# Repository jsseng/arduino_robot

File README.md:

arduino_robot
=============

A controllable arduino robot aimed towards elementary students to get them introduced
to computing at an early age. Comes with firmware and software including a
custom programming language tailored for simple use by students. The grammar
is defined [here](PurelyGrammar.pdf).

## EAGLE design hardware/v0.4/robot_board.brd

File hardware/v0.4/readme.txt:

Note:  Excellon drill file resolution at 5 digits

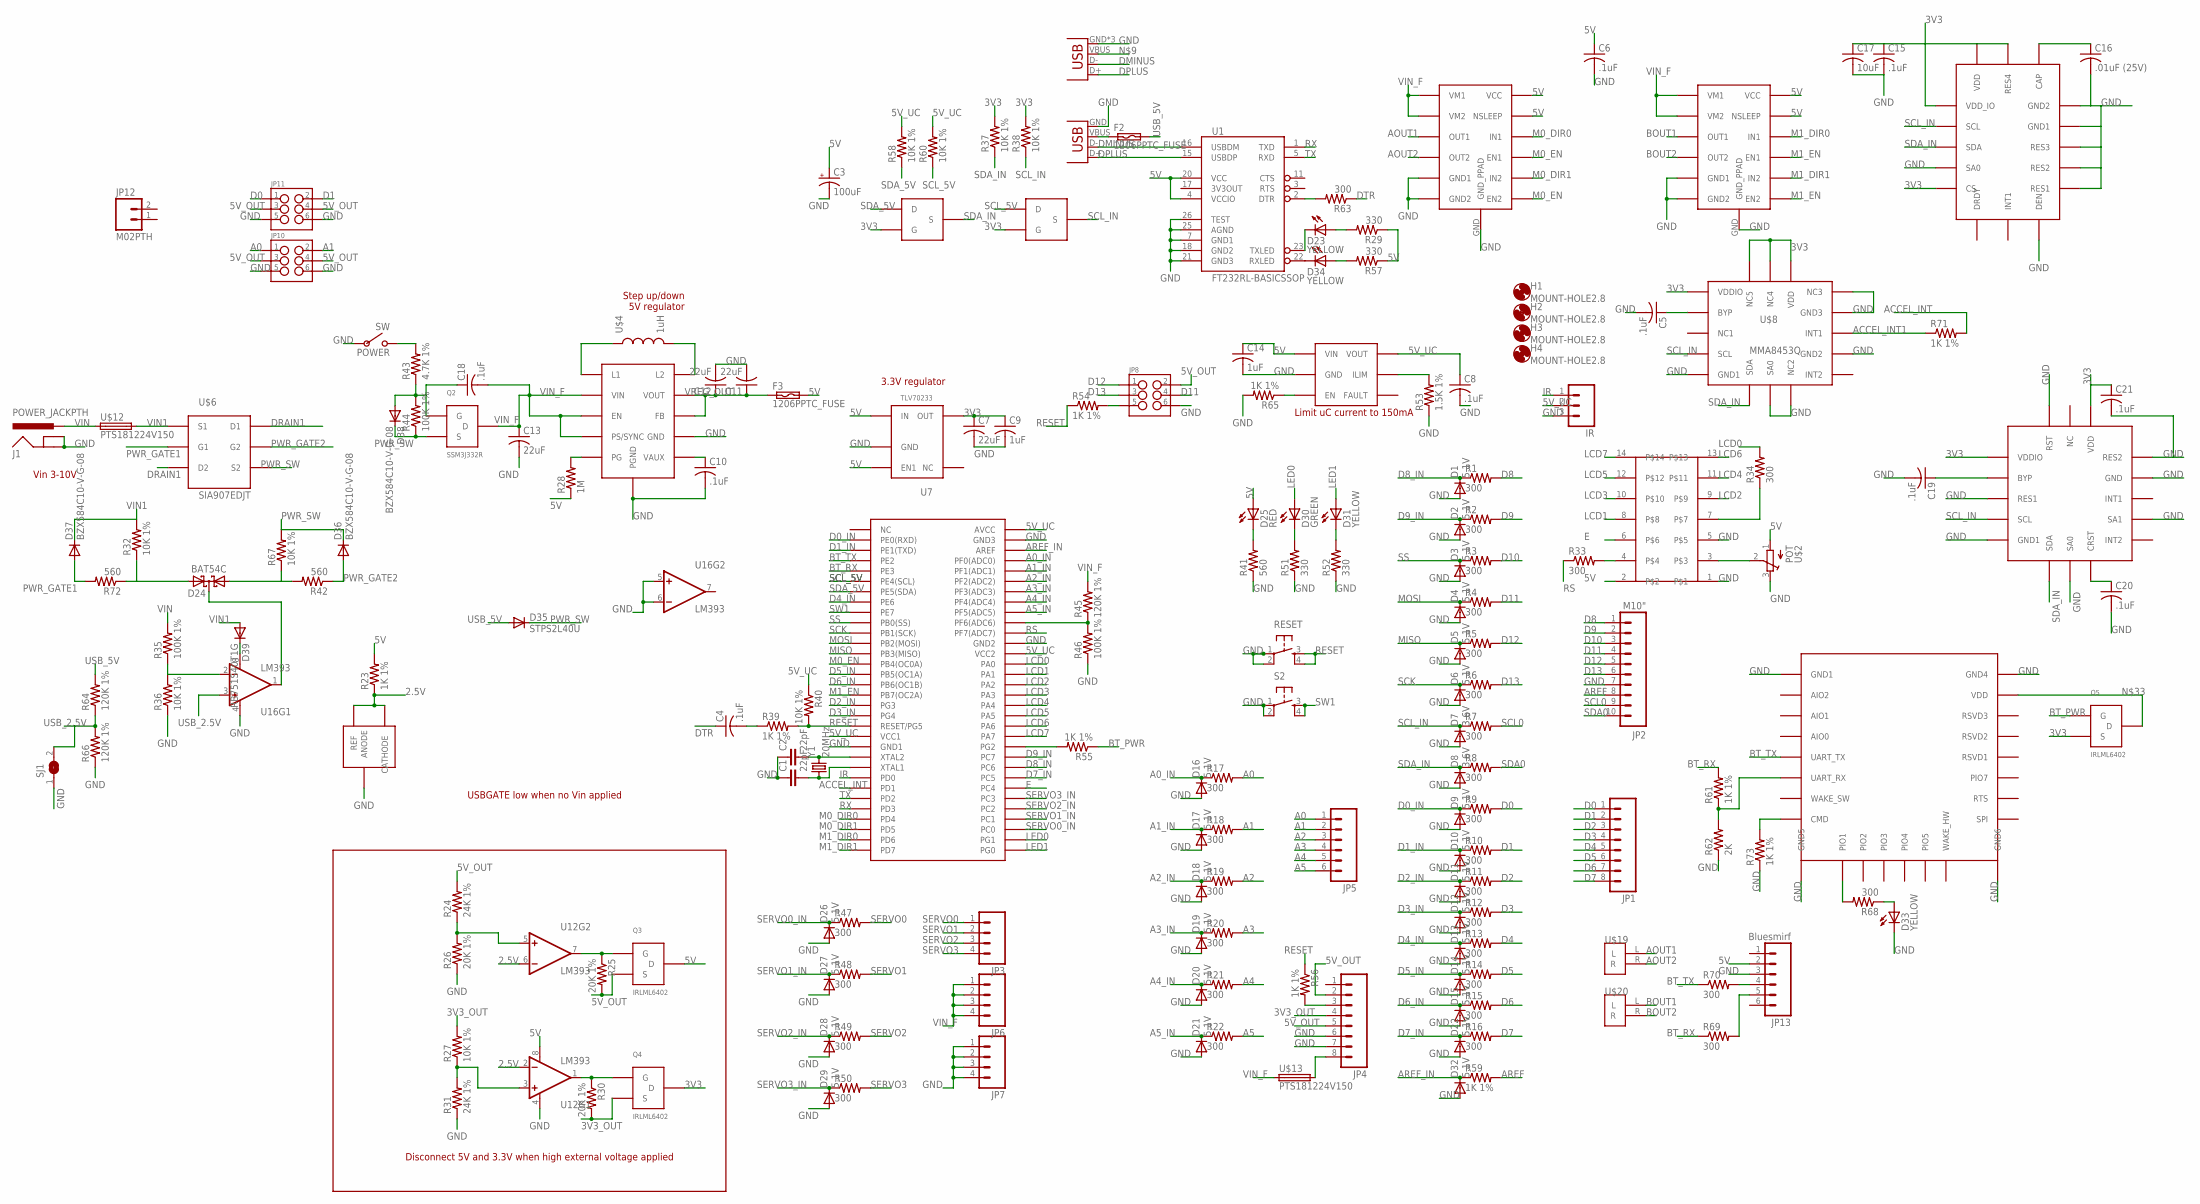
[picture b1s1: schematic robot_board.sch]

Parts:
C1, C2: 22pF; 0805
C3: 100uF; PANASONIC_D
C4, C5, C6, C8, C10, C15, C18, C19, C20, C21: .1uF; C1206
C7, C11, C12, C13: 22uF; C1206
C9, C14: 1uF; C1206
C16: .01uF (25V); C1206
C17: 10uF; C1206
D1, D2, D3, D4, D5, D6, D9, D10, D11, D12, D13, D14, D15, D16, D17, D18, D19, D20, D21, D22, D26, D27, D28, D29, D32: 5.1V; SOT23-3
D7, D8: 3.6V; SOT23-3
D23, D31, D33, D34: YELLOW; LED-1206
D24: BAT54C; SOT23
D25: RED; LED-1206
D30: GREEN; LED-1206
D35: STPS2L40U; SMA-DIODE
D36, D37, D38: BZX584C10-V-G-08; SOD523
D39: RB751S40T1G; SOD523
F2, F3: 1206PPTC_FUSE; R1206
H1, H2, H3, H4: MOUNT-HOLE2.8; 2,8
IR: M03PTH; 1X03
J1: POWER_JACKPTH; POWER_JACK_PTH
JP1, JP4: M081X08; 1X08
JP2: M10"; 1X10
JP3, JP6, JP7: M04PTH; 1X04
JP5: M06SIP; 1X06
JP8, JP10, JP11: M03X22X3_SILK_SM; 2X3
JP9: USB-B; USB-B-PTH
JP12: M02PTH; 1X02
JP13: Bluesmirf; 1X06
JP14: USB-MICROB
POWER: SW
Q2: SSM3J332R; SOT23
Q3, Q4, Q5: IRLML6402; SOT23
R1, R2, R3, R4, R5, R6, R7, R8, R9, R10, R11, R12, R13, R14, R15, R16, R17, R18, R19, R20, R21, R22, R33, R34, R47, R48, R49, R50, R63, R68, R69, R70: 300; R1206
R23, R39, R54, R55, R56, R59, R61, R65, R71, R73: 1K 1%; R1206
R24, R31: 24K 1%; R1206
R25, R26, R30: 20K 1%; R1206
R27, R32, R36, R37, R38, R40, R58, R60, R67: 10K 1%; R1206
R28: 1M; R1206
R29, R51, R52, R57: 330; R1206
R35, R44, R46: 100K 1%; R1206
R41, R42, R72: 560; R1206
R43: 4.7K 1%; R1206
R45, R64, R66: 120K 1%; R1206
R53: 1.5K 1%; R1206
R62: 2K; R1206
RESET: TAC_SWITCHPTH; TACTILE-PTH
S2: TAC_SWITCHPTH; TACTILE-PTH
SJ1: SJW
U1: FT232RL-BASICSSOP; SSOP28DB
U7: TLV70233; SOT-23-5
U8: MIC2009A; SOT23-M5
U9, U10: DRV8839; PWSON-N12
U12, U16: LM393; SO08
U17: ATMEGA325PA; TQFP64
U$1: 2X7HEADER; 2X7
U$2: POT
U$3: TPS63061; WSON-10
U$4: 1uH; TAIYO4012
U$5: AP431SAG-7; SOT23
U$6: SIA907EDJT; SC70T
U$7: RN4020; RN4020_PKG
U$8: MMA8453Q; QFN-COL
U$9, U$10: BSS138; SOT23
U$11: L3GD20HTR; LGA-16
U$12, U$13: PTS181224V150; C1812
U$14: FXOS8700CQ; FSOS8700CQ_PKG
U$19, U$20: 2POS_TERMINAL
Y1: 20MHz; CRYSTAL-SMD-10.5X4.8-2PIN

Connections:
2.5V: R23.1, U12.2 (-IN), U12.6 (-IN), U$5.1 (CATHODE), U$5.2 (REF)
3V3: C7.1, C9.1, C15.1, C17.1, C21.1, Q4.3 (D), Q5.2 (S), R37.2, R38.2, U7.P$4 (OUT), U$8.P$1 (VDDIO), U$8.P$14 (VDD), U$8.P$15 (NC4), U$8.P$16 (NC5), U$9.1 (G), U$10.1 (G), U$11.P$1 (VDD_IO), U$11.P$5 (CS), U$11.P$15 (RES4), U$11.P$16 (VDD), U$14.P$1 (VDDIO), U$14.P$14 (VDD)
3V3_OUT: JP4.4, Q4.2 (S), R27.2, R30.2
5V: C3.+, C6.1, C14.1, D25.A, F3.2, JP13.2, Q3.3 (D), R23.2, R28.1, R29.1, R57.1, U1.4 (VCCIO), U1.20 (VCC), U7.P$1 (IN), U7.P$3 (EN1), U8.P$1 (VIN), U9.P$7 (VCC), U9.P$8 (NSLEEP), U10.P$7 (VCC), U10.P$8 (NSLEEP), U12.8 (V+), U$1.2, U$2.1 (A)
5V_OUT: JP4.2, JP4.5, JP8.2, JP10.3, JP10.4, JP11.3, JP11.4, Q3.2 (S), R24.2, R25.2
5V_UC: C8.1, IR.2, R40.1, R58.2, R60.2, U8.P$6 (VOUT), U17.21 (VCC1), U17.52 (VCC2), U17.64 (AVCC)
A0: JP5.1, JP10.1, R17.2
A0_IN: D16.3 (C), R17.1, U17.61 (PF0(ADC0))
A1: JP5.2, JP10.2, R18.2
A1_IN: D17.3 (C), R18.1, U17.60 (PF1(ADC1))
A2: JP5.3, R19.2
A2_IN: D18.3 (C), R19.1, U17.59 (PF2(ADC2))
A3: JP5.4, R20.2
A3_IN: D19.3 (C), R20.1, U17.58 (PF3(ADC3))
A4: JP5.5, R21.2
A4_IN: D20.3 (C), R21.1, U17.57 (PF4(ADC4))
A5: JP5.6, R22.2
A5_IN: D21.3 (C), R22.1, U17.56 (PF5(ADC5))
ACCEL_INT: R71.2, U17.26 (PD1)
ACCEL_INT1: R71.1, U$8.P$11 (INT1)
AOUT1: U9.P$3 (OUT1), U$19.L
AOUT2: U9.P$4 (OUT2), U$19.R
AREF: JP2.8, R59.2
AREF_IN: D32.3 (C), R59.1, U17.62 (AREF)
BOUT1: U10.P$3 (OUT1), U$20.L
BOUT2: U10.P$4 (OUT2), U$20.R
BT_PWR: Q5.1 (G), R55.1
BT_RX: R61.2, R69.1, U17.5 (PE3)
BT_TX: R70.1, U17.4 (PE2), U$7.P$5 (UART_TX)
D0: JP1.1, JP11.1, R9.2
D0_IN: D9.3 (C), R9.1, U17.2 (PE0(RXD))
D1: JP1.2, JP11.2, R10.2
D1_IN: D10.3 (C), R10.1, U17.3 (PE1(TXD))
D2: JP1.3, R11.2
D2_IN: D11.3 (C), R11.1, U17.18 (PG3)
D3: JP1.4, R12.2
D3_IN: D12.3 (C), R12.1, U17.19 (PG4)
D4: JP1.5, R13.2
D4_IN: D13.3 (C), R13.1, U17.8 (PE6)
D5: JP1.6, R14.2
D5_IN: D14.3 (C), R14.1, U17.15 (PB5(OC1A))
D6: JP1.7, R15.2
D6_IN: D15.3 (C), R15.1, U17.16 (PB6(OC1B))
D7: JP1.8, R16.2
D7_IN: D22.3 (C), R16.1, U17.40 (PC5)
D8: JP2.1, R1.2
D8_IN: D1.3 (C), R1.1, U17.41 (PC6)
D9: JP2.2, R2.2
D9_IN: D2.3 (C), R2.1, U17.42 (PC7)
D10: JP2.3, R3.2
D11: JP2.4, JP8.4, R4.2
D12: JP2.5, JP8.1, R5.2
D13: JP2.6, JP8.3, R6.2
DMINUS: JP9.D-, JP14.D-, U1.16 (USBDM)
DPLUS: JP9.D+, JP14.D+, U1.15 (USBDP)
DRAIN1: U$6.D1@1 (D1), U$6.D1@2 (D1), U$6.D2@1 (D2), U$6.D2@2 (D2)
DTR: C4.1, R63.1
E: U17.39 (PC4), U$1.6
GND: C1.1, C2.1, C3.-, C5.2, C6.2, C7.2, C8.2, C9.2, C10.2, C11.2, C12.2, C13.2, C14.2, C15.2, C16.2, C17.2, C19.2, C20.2, C21.2, D1.1 (A), D2.1 (A), D3.1 (A), D4.1 (A), D5.1 (A), D6.1 (A), D7.1 (A), D8.1 (A), D9.1 (A), D10.1 (A), D11.1 (A), D12.1 (A), D13.1 (A), D14.1 (A), D15.1 (A), D16.1 (A), D17.1 (A), D18.1 (A), D19.1 (A), D20.1 (A), D21.1 (A), D22.1 (A), D26.1 (A), D27.1 (A), D28.1 (A), D29.1 (A), D32.1 (A), D33.C, IR.3, J1.GND, J1.GNDBREAK, JP2.7, JP4.6, JP4.7, JP7.1, JP7.2, JP7.3, JP7.4, JP8.6, JP9.GND, JP10.5, JP10.6, JP11.5, JP11.6, JP13.3, JP14.GND, JP14.MT1 (GND), JP14.MT2 (GND), POWER.P$2, R26.1, R31.1, R36.1, R41.1, R46.1, R51.1, R52.1, R53.1, R62.1, R65.2, R66.1, R73.1, RESET.1, RESET.2, S2.1, S2.2, SJ1.1, U1.7 (GND1), U1.18 (GND2), U1.21 (GND3), U1.25 (AGND), U1.26 (TEST), U7.P$2 (GND), U8.P$2 (GND), U9.GND (GND_PPAD), U9.P$5 (GND1), U9.P$6 (GND2), U10.GND (GND_PPAD), U10.P$5 (GND1), U10.P$6 (GND2), U12.4 (V-), U16.4 (V-), U16.5 (+IN), U16.6 (-IN), U17.22 (GND1), U17.53 (GND2), U17.63 (GND3), U$1.1, U$1.5, U$2.3 (E), U$3.GND@N1 (PGND), U$3.GND@N2 (PGND), U$3.GND@N3 (PGND), U$3.GND@N4 (PGND), U$3.GND@N5 (PGND), U$3.GND@N6 (PGND), U$3.GND@N7 (PGND), U$3.GND@N8 (PGND), U$3.P$7 (GND), U$3.P$11 (PGND), U$5.3 (ANODE), U$7.P$1 (GND1), U$7.P$22 (GND4), U$7.P$23 (GND5), U$7.P$24 (GND6), U$8.P$5 (GND1), U$8.P$7 (SA0), U$8.P$8 (NC2), U$8.P$10 (GND2), U$8.P$12 (GND3), U$8.P$13 (NC3), U$11.P$4 (SA0), U$11.P$8 (DEN), U$11.P$9 (RES1), U$11.P$10 (RES2), U$11.P$11 (RES3), U$11.P$12 (GND1), U$11.P$13 (GND2), U$14.P$3 (RES1), U$14.P$5 (GND1), U$14.P$7 (SA0), U$14.P$10 (SA1), U$14.P$12 (GND), U$14.P$13 (RES2), U$14.P$16 (RST)
IR: IR.1, U17.25 (PD0)
LCD0: R34.2, U17.51 (PA0)
LCD1: U17.50 (PA1), U$1.8
LCD2: U17.49 (PA2), U$1.9
LCD3: U17.48 (PA3), U$1.10
LCD4: U17.47 (PA4), U$1.11
LCD5: U17.46 (PA5), U$1.12
LCD6: U17.45 (PA6), U$1.13
LCD7: U17.44 (PA7), U$1.14
LED0: D30.A, U17.34 (PG1)
LED1: D31.A, U17.33 (PG0)
M0_DIR0: U9.P$9 (IN1), U17.29 (PD4)
M0_DIR1: U9.P$11 (IN2), U17.30 (PD5)
M0_EN: U9.P$10 (EN1), U9.P$12 (EN2), U17.14 (PB4(OC0A))
M1_DIR0: U10.P$9 (IN1), U17.31 (PD6)
M1_DIR1: U10.P$11 (IN2), U17.32 (PD7)
M1_EN: U10.P$10 (EN1), U10.P$12 (EN2), U17.17 (PB7(OC2A))
MISO: D5.3 (C), R5.1, U17.13 (PB3(MISO))
MOSI: D4.3 (C), R4.1, U17.12 (PB2(MOSI))
unnamed: C2.2, U17.23 (XTAL2), Y1.P$2 (2)
unnamed: C1.2, U17.24 (XTAL1), Y1.P$1 (1)
unnamed: R53.2, U8.P$5 (ILIM)
unnamed: R55.2, U17.43 (PG2)
unnamed: JP4.3, R56.2
unnamed: C5.1, U$8.P$2 (BYP)
unnamed: F2.1, JP9.VBUS, JP14.VBUS
unnamed: D34.C, U1.22 (RXLED)
unnamed: D34.A, R57.2
unnamed: D23.A, R29.2
unnamed: R61.1, R62.2, U$7.P$6 (UART_RX)
unnamed: R63.2, U1.2 (DTR)
unnamed: U$1.3, U$2.2 (S)
unnamed: R28.2, U$3.P$5 (PG)
unnamed: R65.1, U8.P$3 (EN)
unnamed: D24.3 (CC), U16.1 (OUT)
unnamed: C10.1, U$3.P$6 (VAUX)
unnamed: U$3.P$1 (L1), U$4.P$1 (1)
unnamed: U$3.P$10 (L2), U$4.P$2 (2)
unnamed: D23.C, U1.23 (TXLED)
unnamed: D24.2 (A2), R32.1, R72.1
unnamed: D24.1 (A1), R42.2, R67.1
unnamed: R33.2, U$1.4
unnamed: R34.1, U$1.7
unnamed: C4.2, R39.1
unnamed: JP4.8, U$13.2
unnamed: JP8.5, R54.2
unnamed: Q3.1 (G), R25.1, U12.7 (OUT)
unnamed: R68.2, U$7.P$9 (PIO1)
unnamed: D33.A, R68.1
unnamed: Q5.3 (D), U$7.P$21 (VDD)
unnamed: R24.1, R26.2, U12.5 (+IN)
unnamed: JP13.4, R70.2
unnamed: JP13.5, R69.2
unnamed: C16.1, U$11.P$14 (CAP)
unnamed: R27.1, R31.2, U12.3 (+IN)
unnamed: R35.1, R36.2, U16.2 (-IN)
unnamed: D25.C, R41.2
unnamed: D39.C, U16.8 (V+)
unnamed: POWER.P$1, R43.2
unnamed: C19.1, U$14.P$2 (BYP)
unnamed: Q4.1 (G), R30.1, U12.1 (OUT)
unnamed: R73.2, U$7.P$8 (CMD)
unnamed: C20.1, U$14.P$8 (CRST)
unnamed: C18.1, D38.A, Q2.1 (G), R43.1, R44.2
unnamed: R45.1, R46.2, U17.55 (PF6(ADC6))
unnamed: D30.C, R51.2
unnamed: D31.C, R52.2
PWR_GATE1: D37.A, R72.2, U$6.G1
PWR_GATE2: D36.A, R42.1, U$6.G2
PWR_SW: D35.C, D36.C, D38.C, Q2.2 (S), R44.1, R67.2, U$6.S2
RESET: R39.2, R40.2, R54.1, R56.1, RESET.3, RESET.4, U17.20 (RESET/PG5)
RS: R33.1, U17.54 (PF7(ADC7))
RX: U1.1 (TXD), U17.28 (PD3)
SCK: D6.3 (C), R6.1, U17.11 (PB1(SCK))
SCL0: JP2.9, R7.2
SCL_5V: R60.1, U17.6 (PE4(SCL)), U$10.3 (D)
SCL_IN: D7.3 (C), R7.1, R38.1, U$8.P$4 (SCL), U$10.2 (S), U$11.P$2 (SCL), U$14.P$4 (SCL)
SDA0: JP2.10, R8.2
SDA_5V: R58.1, U17.7 (PE5(SDA)), U$9.3 (D)
SDA_IN: D8.3 (C), R8.1, R37.1, U$8.P$6 (SDA), U$9.2 (S), U$11.P$3 (SDA), U$14.P$6 (SDA)
SERVO0: JP3.1, R47.2
SERVO0_IN: D26.3 (C), R47.1, U17.35 (PC0)
SERVO1: JP3.2, R48.2
SERVO1_IN: D27.3 (C), R48.1, U17.36 (PC1)
SERVO2: JP3.3, R49.2
SERVO2_IN: D28.3 (C), R49.1, U17.37 (PC2)
SERVO3: JP3.4, R50.2
SERVO3_IN: D29.3 (C), R50.1, U17.38 (PC3)
SS: D3.3 (C), R3.1, U17.10 (PB0(SS))
SW1: S2.3, S2.4, U17.9 (PE7)
TX: U1.5 (RXD), U17.27 (PD2)
USB_2.5V: R64.1, R66.2, SJ1.2, U16.3 (+IN)
USB_5V: D35.A, F2.2, R64.2
VIN: J1.PWR, R35.2, U$12.1
VIN1: D37.C, D39.A, R32.2, U$6.S1, U$12.2
VIN_F: C13.1, C18.2, JP6.1, JP6.2, JP6.3, JP6.4, Q2.3 (D), R45.2, U9.P$1 (VM1), U9.P$2 (VM2), U10.P$1 (VM1), U10.P$2 (VM2), U$3.P$2 (VIN), U$3.P$3 (EN), U$3.P$4 (PS/SYNC), U$13.1
VREG_OUT: C11.1, C12.1, F3.1, U$3.P$8 (FB), U$3.P$9 (VOUT)

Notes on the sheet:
USBGATE low when no Vin applied
3.3V regulator
Disconnect 5V and 3.3V when high external voltage applied
Limit uC current to 150mA
Step up/down 5V regulator
Vin 3-10V

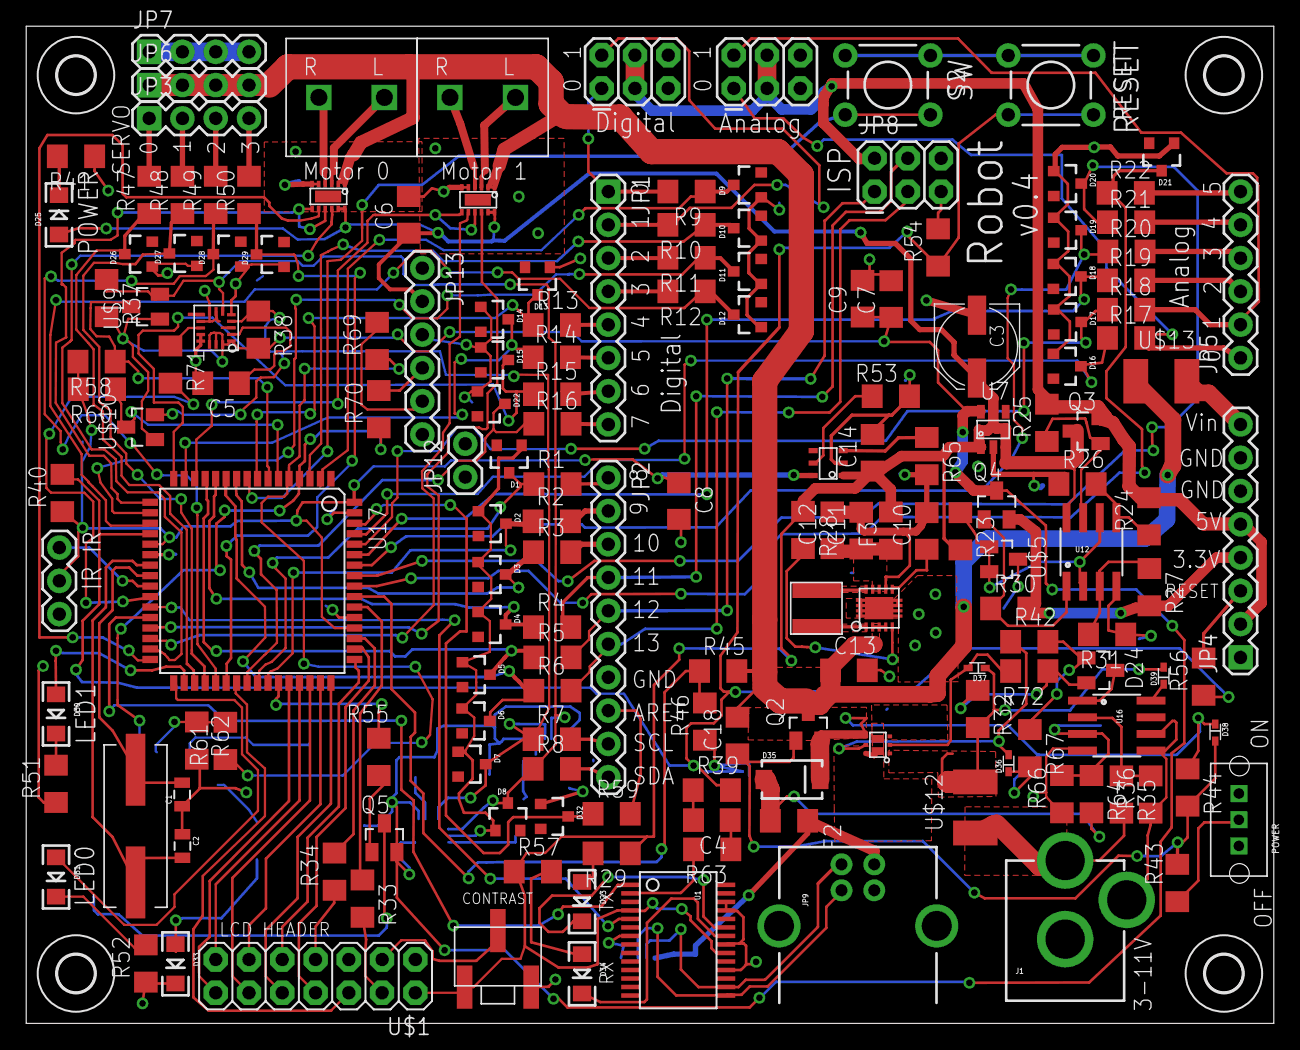
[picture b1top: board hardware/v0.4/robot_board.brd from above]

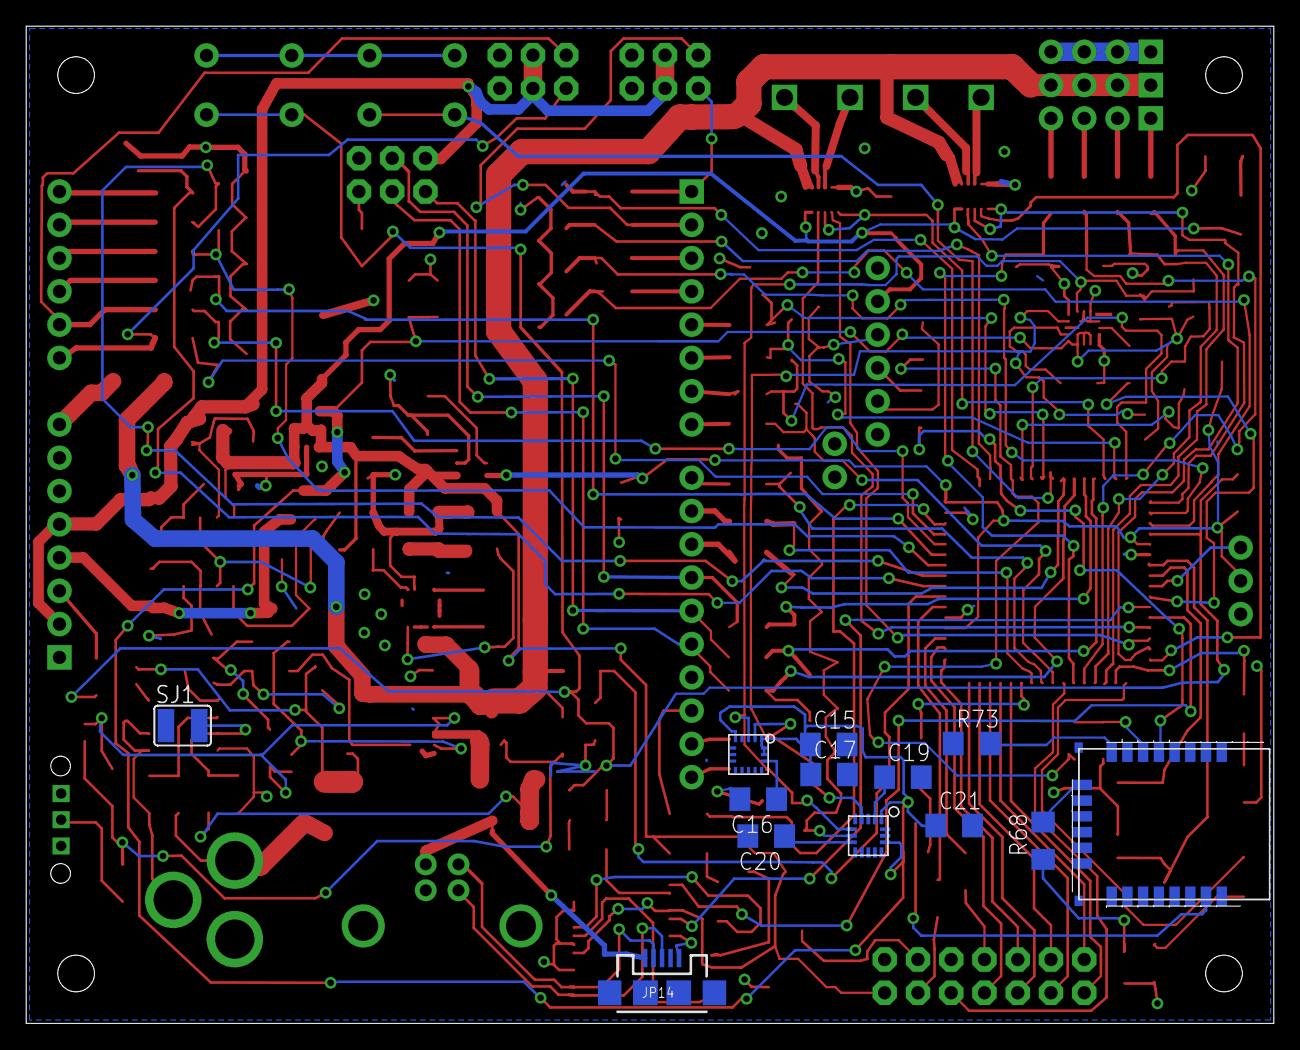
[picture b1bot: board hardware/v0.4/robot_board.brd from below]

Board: 2 copper layers, 95.2 x 76.1 mm, 188 parts (13 on the bottom side), 156 nets.

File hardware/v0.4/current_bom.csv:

"Qty";"Value";"Device";"Package";"Parts";"Description";"PROD_ID";"VALUE";
"1";"";"M03PTH";"1X03";"IR";"Header 3";"";"";
"3";"";"M03X22X3_SILK_SM";"2X3";"JP8, JP10, JP11";"2x3 .1" header.";"";"";
"3";"";"M04PTH";"1X04";"JP3, JP6, JP7";"Header 4";"";"";
"1";"";"M06SIP";"1X06";"JP5";"Header 6";"";"";
"2";"";"M081X08";"1X08";"JP1, JP4";"Header 8";"";"";
"2";"";"TAC_SWITCHPTH";"TACTILE-PTH";"RESET, S2";"Momentary Switch";"";"";
"5";".1uF";"C-USC1206";"C1206";"C4, C5, C6, C8, C10";"CAPACITOR, American symbol";"";"";
"1";"1.5K 1%";"R-US_R1206";"R1206";"R53";"RESISTOR, American symbol";"";"";
"2";"100K 1%";"R-US_R1206";"R1206";"R44, R46";"RESISTOR, American symbol";"";"";
"1";"100uF";"CAP_POLD";"PANASONIC_D";"C3";"Capacitor Polarized";"";"";
"7";"10K 1%";"R-US_R1206";"R1206";"R27, R37, R38, R40, R42, R58, R60";"RESISTOR, American symbol";"";"";
"3";"1206PPTC_FUSE";"1206PPTC_FUSE";"R1206";"F1, F2, F3";"";"";"";
"4";"120K 1%";"R-US_R1206";"R1206";"R35, R45, R64, R66";"RESISTOR, American symbol";"";"";
"1";"16MHz";"CRYSTAL10.5X4.8";"CRYSTAL-SMD-10.5X4.8-2PIN";"Y1";"Various standard crystals. Proven footprints. Spark Fun Electronics SKU : COM-00534";"";"";
"9";"1K 1%";"R-US_R1206";"R1206";"R23, R39, R43, R54, R55, R56, R59, R61, R65";"RESISTOR, American symbol";"";"";
"1";"1M";"R-US_R1206";"R1206";"R28";"RESISTOR, American symbol";"";"";
"2";"1uF";"C-USC1206";"C1206";"C9, C14";"CAPACITOR, American symbol";"";"";
"1";"1uH";"TAIYO4012";"TAIYO4012";"U$4";"";"";"";
"4";"20K 1%";"R-US_R1206";"R1206";"R25, R26, R30, R32";"RESISTOR, American symbol";"";"";
"2";"22pF";"CAP0805";"0805";"C1, C2";"Capacitor";"";"";
"4";"22uF";"C-USC1206";"C1206";"C7, C11, C12, C13";"CAPACITOR, American symbol";"";"";
"2";"24K 1%";"R-US_R1206";"R1206";"R24, R31";"RESISTOR, American symbol";"";"";
"1";"2K";"R-US_R1206";"R1206";"R62";"RESISTOR, American symbol";"";"";
"2";"2POS_TERMINAL";"2POS_TERMINAL";"2POS_TERMINAL";"U$19, U$20";"";"";"";
"1";"2X7HEADER";"2X7HEADER";"2X7";"U$1";"";"";"";
"29";"300";"R-US_R1206";"R1206";"R1, R2, R3, R4, R5, R6, R7, R8, R9, R10, R11, R12, R13, R14, R15, R16, R17, R18, R19, R20, R21, R22, R33, R34, R47, R48, R49, R50, R63";"RESISTOR, American symbol";"";"";
"5";"330";"R-US_R1206";"R1206";"R29, R41, R51, R52, R57";"RESISTOR, American symbol";"";"";
"27";"5.1V";"DIODESOT23";"SOT23-3";"D1, D2, D3, D4, D5, D6, D7, D8, D9, D10, D11, D12, D13, D14, D15, D16, D17, D18, D19, D20, D21, D22, D26, D27, D28, D29, D32";"Diode";"";"";
"1";"604K 1%";"R-US_R1206";"R1206";"R36";"RESISTOR, American symbol";"";"";
"1";"AP431SAG-7";"AP431SAG-7";"SOT23";"U$5";"";"";"";
"1";"ATMEGA325PA";"ATMEGA325PA";"TQFP64";"U17";"";"";"";
"1";"BAT54C";"BAT54C";"SOT23";"D24";"Schottky Diodes";"";"";
"3";"BSS138";"BSS138";"SOT23";"U$9, U$10, U$11";"";"";"";
"4";"DMP2035U";"DMP2035U";"SOT23";"Q1, Q2, Q3, Q4";"Diodes Inc. DMP2035U-7 P-channel logic level mosfet";"";"";
"2";"DRV8839";"DRV8839";"PWSON-N12";"U9, U10";"";"";"";
"1";"FT232RL-BASICSSOP";"FT232RL-BASICSSOP";"SSOP28DB";"U1";"USB UART";"";"";
"1";"GREEN";"LED-GREENLILYPAD";"LED-1206";"D30";"Various green LEDs";"DIO-09910";"GREEN";
"1";"HC_05";"HC_05";"BLUETOOTH_SMD";"U4";"";"";"";
"2";"LM393";"LM393";"SO08";"U12, U16";"Low-voltage comparator";"";"";
"1";"M02PTH";"M02PTH";"1X02";"JP12";"Standard 2-pin 0.1" header. Use with";"";"";
"1";"M10"";"M10"";"1X10";"JP2";"Header 10";"";"";
"1";"MIC2009A";"MIC2009A";"SOT23-M5";"U8";"";"";"";
"1";"MMA8453Q";"MMA8453Q";"QFN-COL";"U$8";"";"";"";
"4";"MOUNT-HOLE2.8";"MOUNT-HOLE2.8";"2,8";"H1, H2, H3, H4";"MOUNTING HOLE with drill center marker";"";"";
"1";"POT";"POT";"POT";"U$2";"";"";"";
"1";"POWER_JACKPTH";"POWER_JACKPTH";"POWER_JACK_PTH";"J1";"Power Jack";"PRT-00119";"";
"1";"PTS181224V150";"PTS181224V150";"C1812";"U$12";"";"";"";
"1";"RED";"LED-GREENLILYPAD";"LED-1206";"D25";"Various green LEDs";"DIO-09910";"GREEN";
"2";"SIA907EDJT";"SIA907EDJT";"SC70T";"U$6, U$7";"";"";"";
"1";"SW";"SW";"SW";"POWER";"";"";"";
"1";"TLV70233";"TLV70233";"SOT-23-5";"U7";"TLV70233 - 3.3V 350mA regulator";"";"";
"1";"TPS63061";"TPS63061";"WSON-10";"U$3";"TPS63031 - Step up/down 5V regulator";"";"";
"1";"USB-B";"USBPTH";"USB-B-PTH";"JP9";"USB Connectors";"CONN-08278";"USB-B";
"3";"YELLOW";"LED-GREENLILYPAD";"LED-1206";"D23, D31, D34";"Various green LEDs";"DIO-09910";"GREEN";

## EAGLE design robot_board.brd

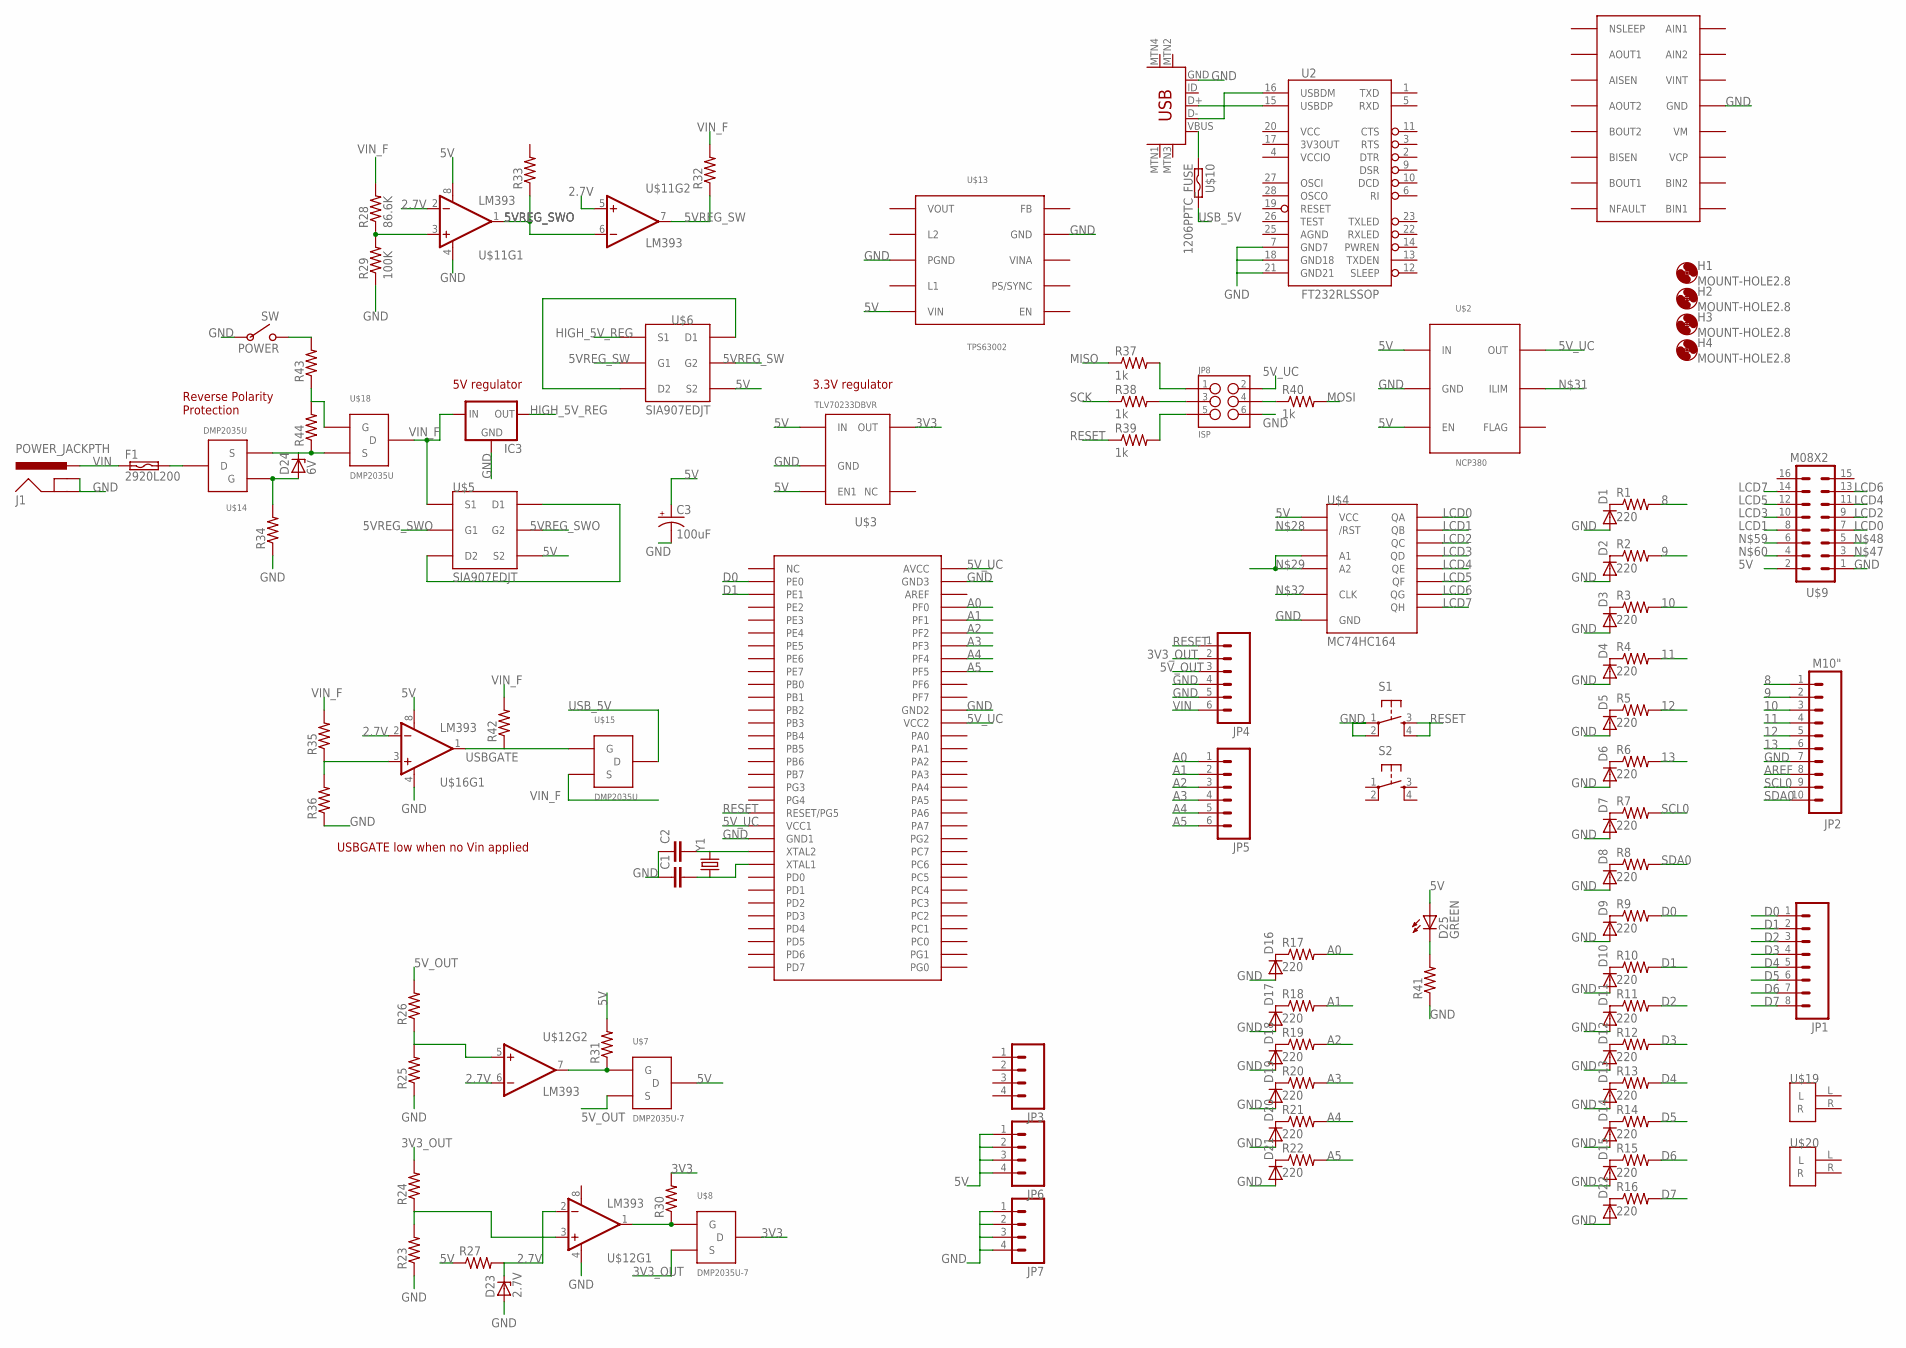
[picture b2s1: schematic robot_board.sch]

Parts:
C1, C2: CAP0805; 0805
C3: 100uF; PANASONIC_D
D1, D2, D3, D4, D5, D6, D7, D8, D9, D10, D11, D12, D13, D14, D15, D16, D17, D18, D19, D20, D21, D22: DIODESOT23; SOT23-3
D23: 2.7V; SOD80C
D24: 6V; SOD80C
D25: GREEN; LED-1206
F1: 2920L200; SMD050F
H1, H2, H3, H4: MOUNT-HOLE2.8; 2,8
IC3: 78XXS
J1: POWER_JACKPTH; POWER_JACK_PTH
JP1: M081X08; 1X08
JP2: M10"; 1X10
JP3, JP6, JP7: M04PTH; 1X04
JP4, JP5: M06SIP; 1X06
JP8: ISP; 2X3
POWER: SW
R1, R2, R3, R4, R5, R6, R7, R8, R9, R10, R11, R12, R13, R14, R15, R16, R17, R18, R19, R20, R21, R22: 220; R1206
R23, R24, R25, R26, R27, R30, R31, R32, R33: R-US_R0805; R0805
R28: 86.6K; R0805
R29: 100K; R0805
R34, R35, R36, R41, R42, R43, R44: R-US_R1206; R1206
R37, R38, R39, R40: 1k; R1206
S1, S2: TAC_SWITCHPTH; TACTILE-PTH
U2: FT232RLSSOP; SSOP28DB
U$1: USB-MINIB-5PIN; USB-MINIB
U$2: NCP380; TSOP-5
U$3: TLV70233DBVR; SOT-23-5
U$4: MC74HC164; TSSOP-14
U$5, U$6: SIA907EDJT; SC70T
U$7, U$8: DMP2035U-7; SOT23
U$9: M08X2; 2X8
U$10: 1206PPTC_FUSE; R1206
U$11, U$12, U$16: LM393; SO08
U$13: TPS63002; 10SON
U$14, U$15, U$18: DMP2035U; SOT23
U$17: ATMEGA325PA; TQFP64
U$19, U$20: 2POS_TERMINAL
U$21: DRV8833; TSSOP16
Y1: CRYSTAL10.5X4.8; CRYSTAL-SMD-10.5X4.8-2PIN

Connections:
2.7V: D23.C, R27.2, U$11.2 (-IN), U$11.5 (+IN), U$12.2 (-IN), U$12.6 (-IN), U$16.2 (-IN)
3V3: R30.2, U$3.P$4 (OUT), U$8.3 (D)
3V3_OUT: JP4.2, R24.2, U$8.2 (S)
5V: C3.+, D25.A, JP6.1, JP6.2, JP6.3, JP6.4, R27.1, R31.2, U$2.P$4 (IN), U$2.P$6 (EN), U$3.P$1 (IN), U$3.P$3 (EN1), U$4.14 (VCC), U$5.P$4 (S2), U$6.P$4 (S2), U$7.3 (D), U$9.2, U$11.8 (V+), U$13.P$5 (VIN), U$16.8 (V+)
5VREG_SW: R32.1, U$6.P$2 (G1), U$6.P$5 (G2), U$11.7 (OUT)
5VREG_SWO: R33.1, U$5.P$2 (G1), U$5.P$5 (G2), U$11.1 (OUT), U$11.6 (-IN)
5V_OUT: JP4.3, R26.2, U$7.2 (S)
5V_UC: JP8.2, U$2.P$1 (OUT), U$17.21 (VCC1), U$17.52 (VCC2), U$17.64 (AVCC)
8: JP2.1, R1.2
9: JP2.2, R2.2
10: JP2.3, R3.2
11: JP2.4, R4.2
12: JP2.5, R5.2
13: JP2.6, R6.2
A0: JP5.1, R17.2, U$17.61 (PF0)
A1: JP5.2, R18.2, U$17.60 (PF1)
A2: JP5.3, R19.2, U$17.59 (PF2)
A3: JP5.4, R20.2, U$17.58 (PF3)
A4: JP5.5, R21.2, U$17.57 (PF4)
A5: JP5.6, R22.2, U$17.56 (PF5)
AGND: U2.25 (AGND)
AREF: JP2.8
D0: JP1.1, R9.2, U$17.2 (PE0)
D1: JP1.2, R10.2, U$17.3 (PE1)
D2: JP1.3, R11.2
D3: JP1.4, R12.2
D4: JP1.5, R13.2
D5: JP1.6, R14.2
D6: JP1.7, R15.2
D7: JP1.8, R16.2
GND: C1.1, C2.1, C3.-, D1.1 (A), D2.1 (A), D3.1 (A), D4.1 (A), D5.1 (A), D6.1 (A), D7.1 (A), D8.1 (A), D9.1 (A), D10.1 (A), D11.1 (A), D12.1 (A), D13.1 (A), D14.1 (A), D15.1 (A), D16.1 (A), D17.1 (A), D18.1 (A), D19.1 (A), D20.1 (A), D21.1 (A), D22.1 (A), D23.A, IC3.GND, J1.GND, J1.GNDBREAK, JP2.7, JP4.4, JP4.5, JP7.1, JP7.2, JP7.3, JP7.4, JP8.6, POWER.P$2, R23.1, R25.1, R29.1, R34.1, R36.1, R41.1, S1.1, S1.2, U2.7 (GND7), U2.18 (GND18), U2.21 (GND21), U$1.GND, U$2.P$5 (GND), U$3.P$2 (GND), U$4.7 (GND), U$9.1, U$11.4 (V-), U$12.4 (V-), U$13.P$3 (PGND), U$13.P$9 (GND), U$16.4 (V-), U$17.22 (GND1), U$17.53 (GND2), U$17.63 (GND3), U$21.13 (GND)
HIGH_5V_REG: IC3.OUT, U$6.P$1 (S1)
LCD0: U$4.3 (QA), U$9.7
LCD1: U$4.4 (QB), U$9.8
LCD2: U$4.5 (QC), U$9.9
LCD3: U$4.6 (QD), U$9.10
LCD4: U$4.10 (QE), U$9.11
LCD5: U$4.11 (QF), U$9.12
LCD6: U$4.12 (QG), U$9.13
LCD7: U$4.13 (QH), U$9.14
MISO: R37.1
MOSI: R40.2
unnamed: U2.16 (USBDM), U$1.D-
unnamed: U2.15 (USBDP), U$1.D+
unnamed: C2.2, Y1.P$2 (2)
unnamed: C1.2, Y1.P$1 (1)
unnamed: D1.3 (C), R1.1
unnamed: D2.3 (C), R2.1
unnamed: D3.3 (C), R3.1
unnamed: D4.3 (C), R4.1
unnamed: D5.3 (C), R5.1
unnamed: D6.3 (C), R6.1
unnamed: D7.3 (C), R7.1
unnamed: D8.3 (C), R8.1
unnamed: D9.3 (C), R9.1
unnamed: D10.3 (C), R10.1
unnamed: D11.3 (C), R11.1
unnamed: D12.3 (C), R12.1
unnamed: D13.3 (C), R13.1
unnamed: D14.3 (C), R14.1
unnamed: D15.3 (C), R15.1
unnamed: D22.3 (C), R16.1
unnamed: D16.3 (C), R17.1
unnamed: D17.3 (C), R18.1
unnamed: D18.3 (C), R19.1
unnamed: D19.3 (C), R20.1
unnamed: D20.3 (C), R21.1
unnamed: D21.3 (C), R22.1
unnamed: U$1.VBUS, U$10.1
unnamed: U$4.1 (A1), U$4.2 (A2)
unnamed: R31.1, U$7.1 (G), U$12.7 (OUT)
unnamed: F1.2, U$14.3 (D)
unnamed: R25.2, R26.1, U$12.5 (+IN)
unnamed: R28.1, R29.2, U$11.3 (+IN)
unnamed: D24.A, R34.2, U$14.1 (G)
unnamed: JP8.4, R40.1
unnamed: R23.2, R24.1, U$12.3 (+IN)
unnamed: R35.1, R36.2, U$16.3 (+IN)
unnamed: D24.C, R44.1, U$14.2 (S), U$18.2 (S)
unnamed: D25.C, R41.2
unnamed: U$6.P$3 (D2), U$6.P$6 (D1)
unnamed: POWER.P$1, R43.2
unnamed: U$5.P$3 (D2), U$5.P$6 (D1)
unnamed: R30.1, U$8.1 (G), U$12.1 (OUT)
unnamed: JP8.5, R39.2
unnamed: JP8.3, R38.2
unnamed: JP8.1, R37.2
unnamed: R43.1, R44.2, U$18.1 (G)
RESET: JP4.1, R39.1, S1.3, S1.4, U$17.20 (RESET/PG5)
SCK: R38.1
SCL0: JP2.9, R7.2
SDA0: JP2.10, R8.2
USBGATE: R42.1, U$15.1 (G), U$16.1 (OUT)
USB_5V: U$10.2, U$15.3 (D)
V+: U$12.8 (V+)
VCC: U2.20 (VCC)
VCCIO: U2.4 (VCCIO)
VIN: F1.1, J1.PWR, JP4.6
VIN_F: IC3.IN, R28.2, R32.2, R35.2, R42.2, U$5.P$1 (S1), U$15.2 (S), U$18.3 (D)

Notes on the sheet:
Reverse Polarity Protection
USBGATE low when no Vin applied
5V regulator
3.3V regulator

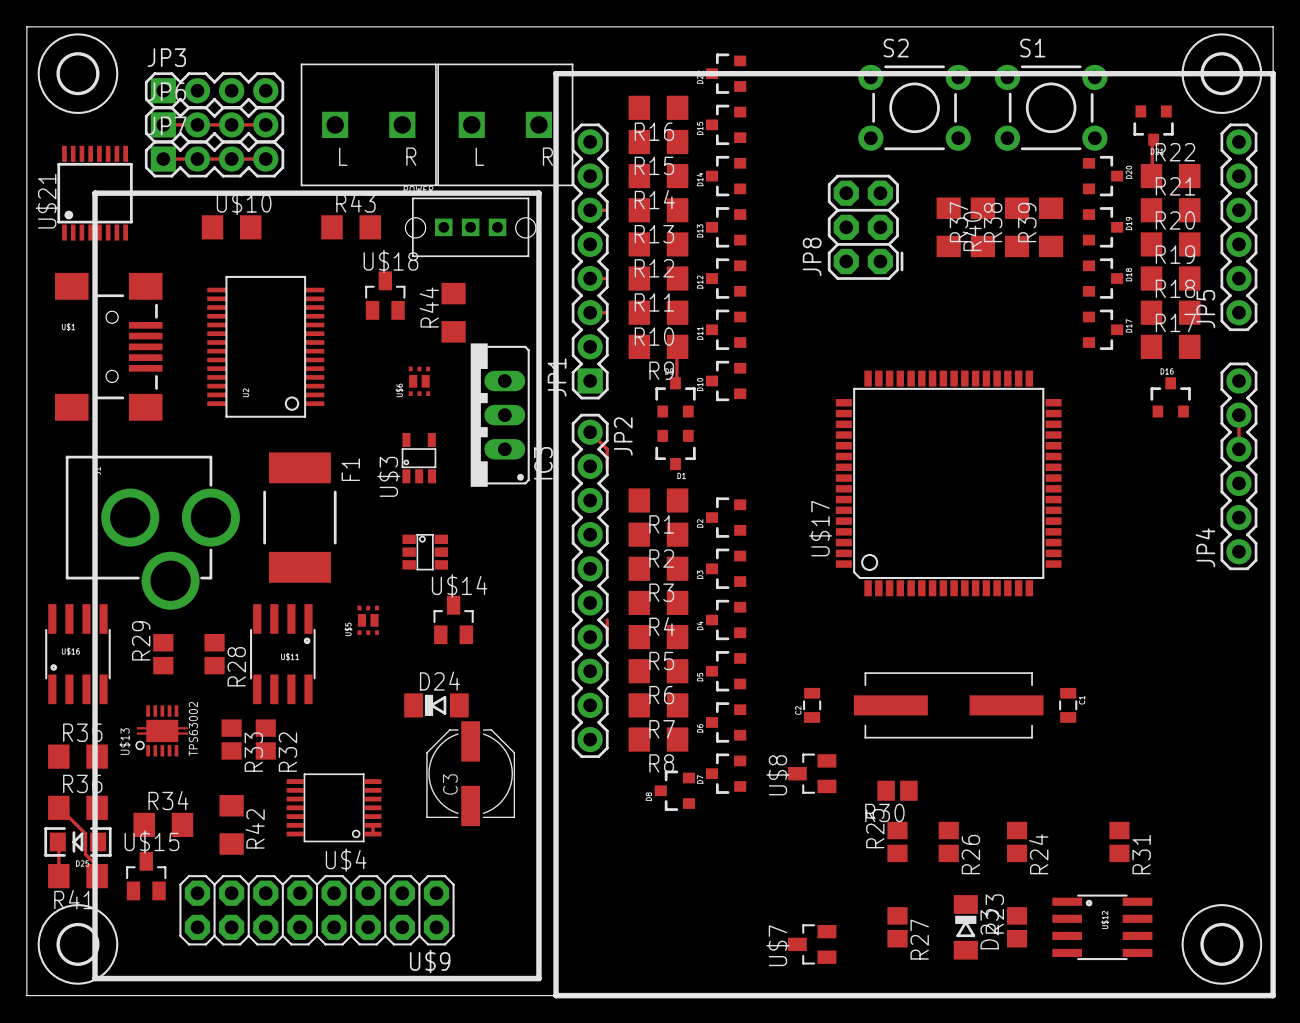
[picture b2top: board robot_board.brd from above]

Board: 2 copper layers, 92.7 x 72.1 mm, 113 parts (0 on the bottom side), 91 nets.

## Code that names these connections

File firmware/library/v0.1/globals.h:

//Global defines

#ifndef GLOBALS_H
#define GLOBALS_H

#define F_CPU 20000000UL //20MHz clock

typedef unsigned char u08;
typedef unsigned int u16;

#define sbi(a, b) (a) |= _BV(b)
#define cbi(a, b) (a) &= ~_BV(b)

#define LCD_E_PIN 0  //PC0
#define LCD_RS_PIN 1 //PC1
#define LCD_DATA_PORT PORTA

#define SW1_PIN 7  //PE7
#define LED0_PIN 0 //PG0
#define LED1_PIN 1 //PG1
#define USB_DETECT_PIN 2 //PG2
#define IR_PIN 0 //PD0
#define ACCEL_INT_PIN 1 //PD1

#define MOTOR0_EN_PIN 4 //PB4
#define MOTOR1_EN_PIN 7 //PB7
#define MOTOR0_DIR0_PIN 4 //PD4
#define MOTOR0_DIR1_PIN 5 //PD5
#define MOTOR1_DIR0_PIN 6 //PD6
#define MOTOR1_DIR1_PIN 7 //PD7

#define DIGITAL0_PIN 0 //PE0
#define DIGITAL1_PIN 1 //PE1
#define DIGITAL2_PIN 3 //PG3
#define DIGITAL3_PIN 4 //PG4
#define DIGITAL4_PIN 6 //PE6
#define DIGITAL5_PIN 5 //PB5
#define DIGITAL6_PIN 6 //PB6
#define DIGITAL7_PIN 5 //PC5
#define DIGITAL8_PIN 6 //PC6
#define DIGITAL9_PIN 7 //PC7
#define DIGITAL10_PIN 0 //PB0/SS
#define DIGITAL11_PIN 2 //PB2/MOSI
#define DIGITAL12_PIN 3 //PB3/MISO
#define DIGITAL13_PIN 1 //PB1/SCK

#define ANALOG0_PIN 0 //PF0
#define ANALOG1_PIN 1 //PF1
#define ANALOG2_PIN 2 //PF2
#define ANALOG3_PIN 3 //PF3
#define ANALOG4_PIN 4 //PF4
#define ANALOG5_PIN 5 //PF5
#define BATTERY_PIN 6 //PF6

#define SERVO0_PIN 2 //PC2
#define SERVO1_PIN 3 //PC3
#define SERVO2_PIN 4 //PC4
#define SERVO3_PIN 7 //PF7

#define SDA_PIN 5
#define SCL_PIN 4
#define I2C_DDR DDRE
#define I2C_PORT PORTE
#define I2C_PIN PINE
#define SDA_HI I2C_DDR &= ~_BV(SDA_PIN); //make as input to set high
#define SCL_HI I2C_DDR &= ~_BV(SCL_PIN); //make as input to set high
#define SDA_LO I2C_DDR |= _BV(SDA_PIN); I2C_PORT &= ~_BV(SDA_PIN); //set as output and write low
#define SCL_LO I2C_DDR |= _BV(SCL_PIN); I2C_PORT &= ~_BV(SCL_PIN); //set as output and write low
#define I2C_DELAY 1
#define MMA8453_ADDR 0x1C

void print_string(char* string, u08 num_bytes);
void i2c_start(void);
void i2c_stop(void);
void unlock_bus(void);
void clock_scl();
void send_address(u08 reg, u08 read);
void write_register(u08* data, u08 num);
void read_register(u08* data, u08 num);

#endif

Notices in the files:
parts and their libraries:
SparkFun-DigitalIC: Licensing: CC v3.0 Share-Alike You are welcome to use this library for commercial purposes.
